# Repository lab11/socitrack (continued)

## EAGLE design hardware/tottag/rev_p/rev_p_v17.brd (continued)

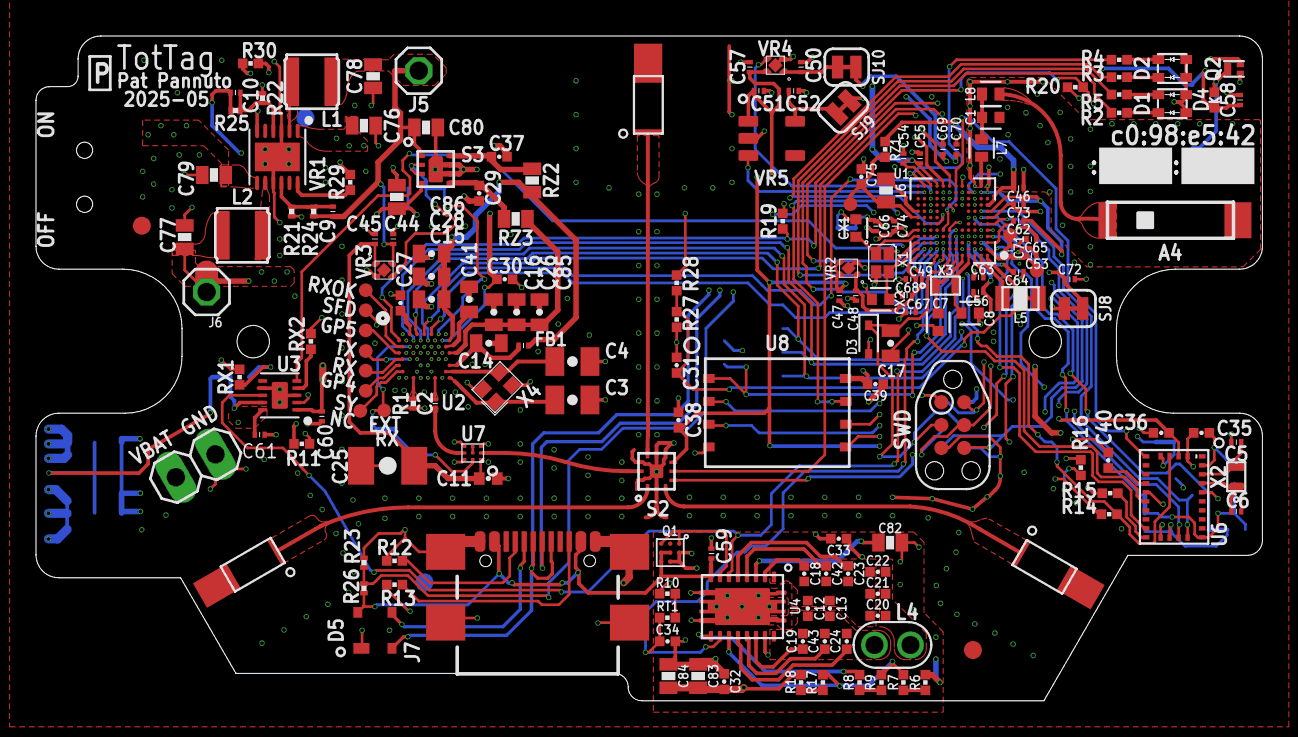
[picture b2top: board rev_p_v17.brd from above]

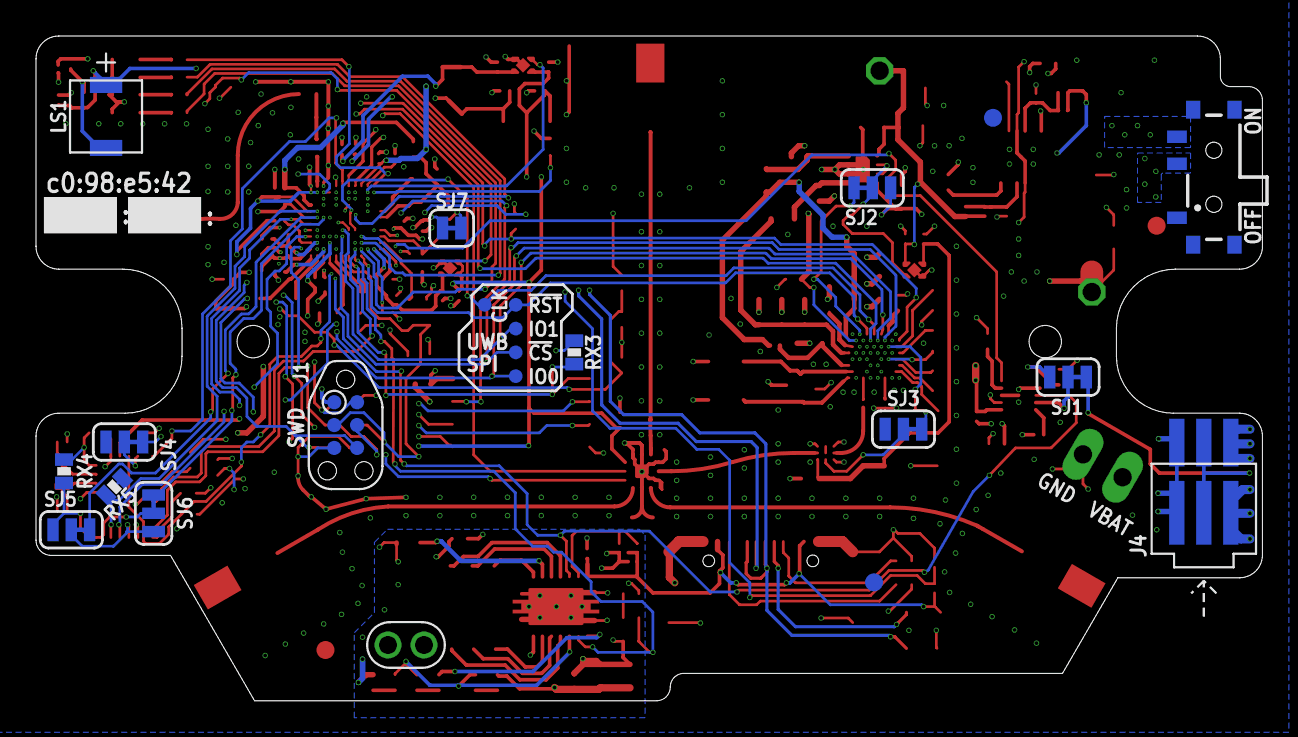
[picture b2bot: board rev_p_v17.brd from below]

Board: 4 copper layers, 68.1 x 36.9 mm, 202 parts (20 on the bottom side), 145 nets.
